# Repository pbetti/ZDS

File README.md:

# ZDS

What you find here are all my stuff about Nuova Elettronica Z80. Software, ideas &amp; projects, both software and hardware.
See more at http://www.z80cpu.eu/projects/14-data-articles/116-z80ne-where-it-all-began

Microcomputer Z80 by Nuova Elettronica

The system consists of dedicated boards. Each card performs a specific function and all the main boards are connected on a propietary bus.
As i found out later, the original design of the system was effectively developed by a company called Micro Design of Genoa and not by Nuova Elettronica.
The orientation however, is to provide an educational system as evidenced by the basic system that consists of the CPU board and an hexadecimal keyboard.
The magazine, however, has introduced later a comprehensive set of additional hardware to allow the construction of a complete system of a level comparable to systems like S-100s or TRS-80 just for an example.
The kits provided by Nuova Elettronica were presented fairly quickly at the beginning and then slow down over time.
The whole system is developed, however, covering a period of considerably long time from 1979 to 1985, which is much greater in life expectancy then today's PC.
The decision to break up the presentation and furniture of the Z80NE hardware, worked well for both the magazine, interested in selling kits and so to maintains high the interest in his system, both for the users who can spread over time the costs (quite remarkable at the end) of buying the whole system and, at the same time, having the time to "assimilate" what the magazine continues to offer in terms of didactic information a kit after another.

The board design is sophisticated and robust, with low component density so to put even the less "technically savvy" people able to mount the components without errors (well... almost).
As to be noticed, not all the hardware presented can be used simultaneously, for example, there are two video interfaces, a low resolution and a hi-res which are mutually incompatible, as well as various memory cards that can only be used in certain configurations to obtain a maximum of up to 56K of RAM which is the limit for our computer. This is because the upper 4kbytes are used by the monitor and lower 4k of RAM (a single kbyte used actually) from E000H to EFFFH is reserved for the lo-res video card.
Another interesting case is the system monitor originally present on the CPU board, which maps 1kb of EPROM at address 8000H, thus blocking any expansion above 32k, chip that infact was removed almost immediately, and placed on the floppy interface card (mapped at F000H).

This apparent schizophrenic design is explained, over the time, with the intent to have a system that users can set up accordingly to their needs and interests.
Even if, i'm willing to bet that the most of them have brought their Z80NE to its maximum potential.
Many of these limitations can easily be overcome with small interventions, as we'll see later.

The system BUS is parallel, consisting of 48 lines divided on two single-in-line connectors of 24 pins each.
The connector "A" drives power (-12V, + 12V, + 5V) and all control signals of Z80 cpu including IEI, IEO pins that should established a daisy-chain interrupt priority between the cards according to the position of insertion, feature never used by Nuova Elettronica, while the connector "B" was dedicated to the address and data lines.

Normally, the power supply and the boards were enclosed in a 5U rack mount black case. This all-black style led me to give to my system the nickname of Z80Darkstar, for which you'll find references in the next articles.

For all details about every board and also original schematics and magazine articles, please, look here: http://www.z80ne.com/eng/hardware.asp

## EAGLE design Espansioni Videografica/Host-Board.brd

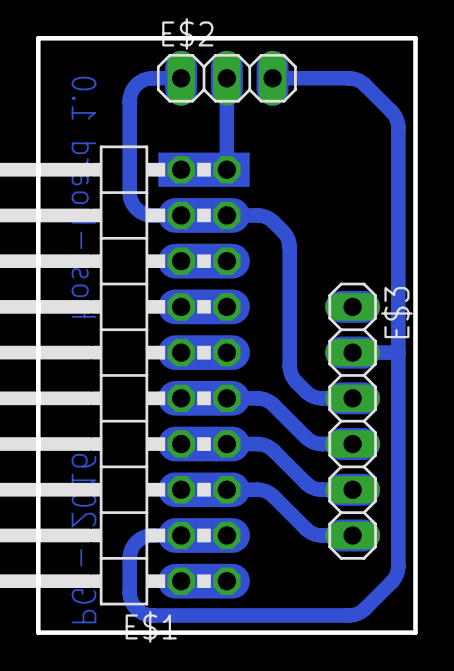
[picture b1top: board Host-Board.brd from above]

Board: 2 copper layers, 21.0 x 33.0 mm, 3 parts (0 on the bottom side), 5 nets.

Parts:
E$1: 2X10/90
E$2: 1X03
E$3: 1X06

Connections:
BUZZER: E$1.19, E$2.2
CE/RST: E$1.5, E$3.6
GND: E$1.1, E$1.17, E$1.18, E$3.3
SCLK: E$1.9, E$3.4
VCC: E$1.4, E$3.2

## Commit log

2016-04-23 Force realigment
2016-04-23 Monitor sources dir reintroducted.
2016-04-24 Optimized gencpm.dat management
2016-04-25 Disk generation reorganized.
2016-05-15 Standard DRI disk images ok.
2016-05-15 Fixed z3plus bootstrap from virtual disks
2016-06-19 Explained 6545 register
2016-07-03 Rewritten CRTC management. Fixed LF/CR bug
2016-07-03 file cleanup
2016-07-17 refined floppy i/o routines. error correctly catched but cp/m 3 still hang on floppy error...
2016-08-21 Release 3.4. Fixed empty floppy drive bug. Still need reboot to see partition table.
2016-09-10 workaround for double hd initialization needed to see partitions. Revision updated to 3.5
2017-01-07 fdisk re-add
2017-01-07 Fixed fdisk to git
2017-04-03 Serial line transfer driver & software added. First version (alpha)
2017-04-03 Fixed file submission
2017-05-18 modified lx529, ep529 char map
2017-05-25 Modified LX529 character generator eproms
2017-11-14 - Almost completed ZMODEM - Start port of NEDOS Basic to CP/M - Some bug fixes
2017-11-14 fixed zmodem tree
2017-11-24 Git branch alignment
2017-12-16 Added dsktran utility, heavy modifications to vdsk_server, initial support for NEDOS, added eprom loaders
2017-12-16 Removed dsktran directory
2018-01-18 Added support dir for external but mandatory tools/libs
2018-03-21 vdsk_server fixing on IMD support. New version 1.8.1
2018-08-15 New version of trampoline
2018-08-16 Standard char print moved in common area to improve speed (no bank switch)
2018-08-16 Fixed new compact trampoline. THIS REQUIRE COMPLETE SW REBUILD.
2018-08-25 - optimized CP/M3 - inserted emdedded debugger for CP/M3 bios - fixed time module bug
2018-08-26 CP/M3 size optimization fix on vdsk_server for skew == 0
2018-08-29 fixed old bug on serial console (data loss on transfer)
2018-08-29 renamed s -> s.static tp recover Udo Munk's git version
2018-08-30 Initial commit for v 4.0.0
2018-08-31 added eeprom programmer as stand alone prog. "flasher"
2018-09-08 v 3.9.2
2018-09-08 zipped vi
2018-09-08 rom image management rewritten
2018-09-13 v3.9.4 fixed serial console for new features
2018-09-20 v3.9.7
2018-09-27 fdisk 1.1, MultiF-Board schematic upgrade
2018-09-30 sdcc cp/m io low level support
2018-10-09 Added CP/M support stdio library for sdcc
2018-11-06 rel 4.0.0
2018-11-07 flasher bug fixed
2018-12-06 Recovered ROM basic
2019-01-03 Porting of Rogue game
2019-02-06 Pre support dual IDE
2019-02-17 v5.0.0 running 32k sysbios
2019-03-11 Dual IDE support in sysbios
2019-03-13 fixing CP/M bugs on new sysbios
2019-03-15 DBG on CP/M
2019-03-31 dual ide CP/M bug fixed
2019-04-14 Dual IDE completed
2019-04-15 Fixed CP/M bug for large cpm3.sys - Mapped 16 drives
2019-04-19 Cleanup
2019-04-29 CF Card support and HD I: image init
2019-04-29 missing cf_init
2019-05-01 Master/slave option for cf_init
2019-05-02 v5.0.1
2019-05-02 fix 5.0.1
2019-05-03 immagine eeprom
2019-05-27 Fixed (probably) cold boot video init. Parallel 2.0 support by default.
2019-07-27 git tree reorg, mbasic project started
2019-07-27 git reorg
2019-07-27 git cleanup
2020-08-25 new work merge
2020-10-16 VGA alt
2020-10-22 replaced with a working copy
    Got from the Z80NE CP/M disk images.
    First pass: disk image converted to RAW with IMDU
    Seconf pass: cpmtools, by adjusting the 'skew' parameter on 'diskdefs' as follows
    diskdef SONE128
    seclen 128
    tracks 40
2020-10-22 More files from Z80NE CP/M disks
